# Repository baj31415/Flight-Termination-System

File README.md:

# FTS
Flight Termination System for SUAS 2018

This is the onboard flight termination system designed for the safety flight termination of an aircraft in the case of a telemetry or rc link loss. This system was used by my team SRMUAV's aircraft in the competition AUVSI SUAS 2018. Completely designed in Eagle CAD.

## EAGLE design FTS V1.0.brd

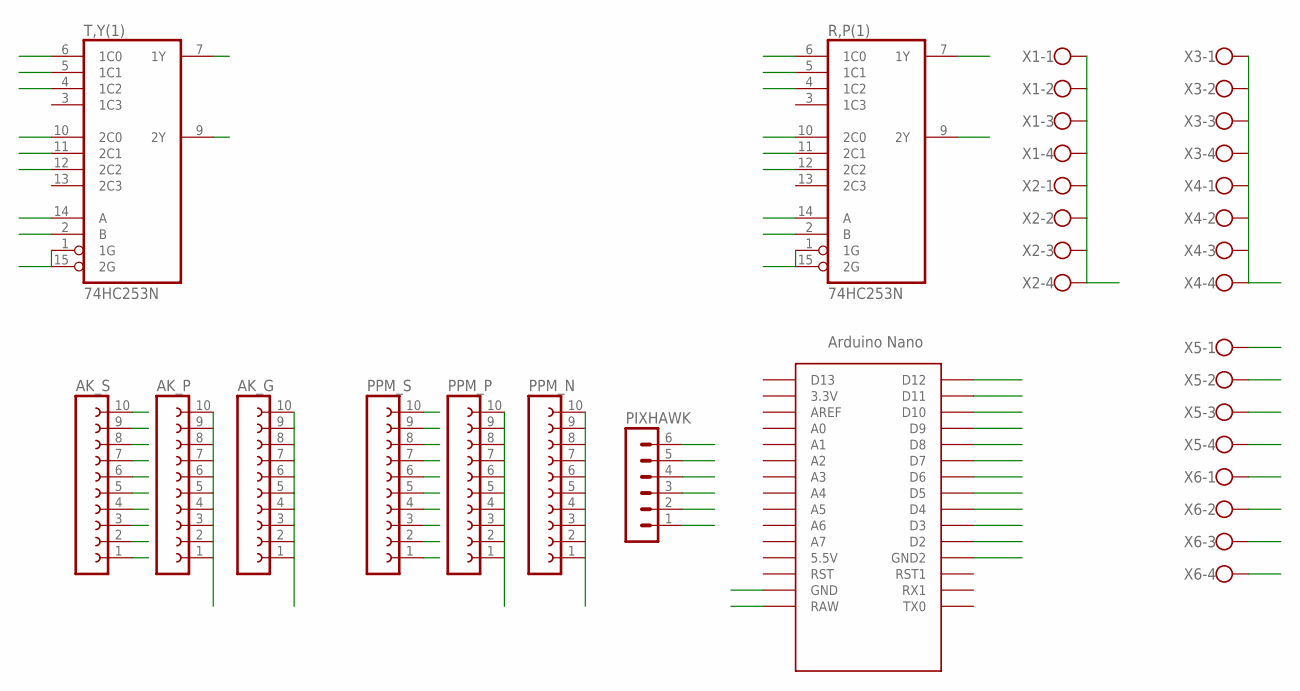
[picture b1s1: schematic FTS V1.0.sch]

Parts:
AK_G: FE10-1; FE10
AK_P: FE10-1; FE10
AK_S: FE10-1; FE10
PIXHAWK: MA06-1
PPM_N: FE10-1; FE10
PPM_P: FE10-1; FE10
PPM_S: FE10-1; FE10
R,P(1): 74HC253N; DIL16
T,Y(1): 74HC253N; DIL16
U$1: NANO
X1, X2, X3, X4, X5, X6: W237-4

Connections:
AUX2: AK_S.7, U$1.D4
DROP: AK_S.10, X6.4
FTS-P: R,P(1).12 (2C2), U$1.D10
FTS-R: R,P(1).4 (1C2), U$1.D9
FTS-T: T,Y(1).4 (1C2), U$1.D11
FTS-Y: T,Y(1).12 (2C2), U$1.D6
GBL-P: AK_S.9, X6.3
GBL-R: AK_S.8, X6.2
GEAR: AK_S.6, U$1.D5
GND: AK_G.1, AK_G.2, AK_G.3, AK_G.4, AK_G.5, AK_G.6, AK_G.7, AK_G.8, AK_G.9, AK_G.10, PIXHAWK.6, PPM_N.1, PPM_N.2, PPM_N.3, PPM_N.4, PPM_N.5, PPM_N.6, PPM_N.7, PPM_N.8, PPM_N.9, PPM_N.10, R,P(1).1 (1G), R,P(1).8 (GND), R,P(1).15 (2G), T,Y(1).1 (1G), T,Y(1).8 (GND), T,Y(1).15 (2G), U$1.GND, U$1.GND1 (GND2), X3.1, X3.2, X3.3, X3.4, X4.1, X4.2, X4.3, X4.4
PPM_FM: PPM_S.5, U$1.D8
PX-P: PIXHAWK.2, R,P(1).11 (2C1)
PX-R: PIXHAWK.1, R,P(1).5 (1C1)
PX-T: PIXHAWK.3, T,Y(1).5 (1C1)
PX-Y: PIXHAWK.4, T,Y(1).11 (2C1)
RX-FM: AK_S.5, U$1.D7
RX-P: AK_S.2, PPM_S.2, R,P(1).10 (2C0)
RX-R: AK_S.1, PPM_S.1, R,P(1).6 (1C0)
RX-T: AK_S.3, PPM_S.3, T,Y(1).6 (1C0), U$1.D12
RX-Y: AK_S.4, PPM_S.4, T,Y(1).10 (2C0)
S1: R,P(1).14 (A), T,Y(1).14 (A), U$1.D2
S2: R,P(1).2 (B), T,Y(1).2 (B), U$1.D3
S-P: R,P(1).9 (2Y), X5.2
S-R: R,P(1).7 (1Y), X5.1
S-T: T,Y(1).7 (1Y), X5.3
S-Y: T,Y(1).9 (2Y), X5.4, X6.1
VCC: AK_P.1, AK_P.2, AK_P.3, AK_P.4, AK_P.5, AK_P.6, AK_P.7, AK_P.8, AK_P.9, AK_P.10, PPM_P.1, PPM_P.2, PPM_P.3, PPM_P.4, PPM_P.5, PPM_P.6, PPM_P.7, PPM_P.8, PPM_P.9, PPM_P.10, R,P(1).16 (VCC), T,Y(1).16 (VCC), U$1.RAW, X1.1, X1.2, X1.3, X1.4, X2.1, X2.2, X2.3, X2.4

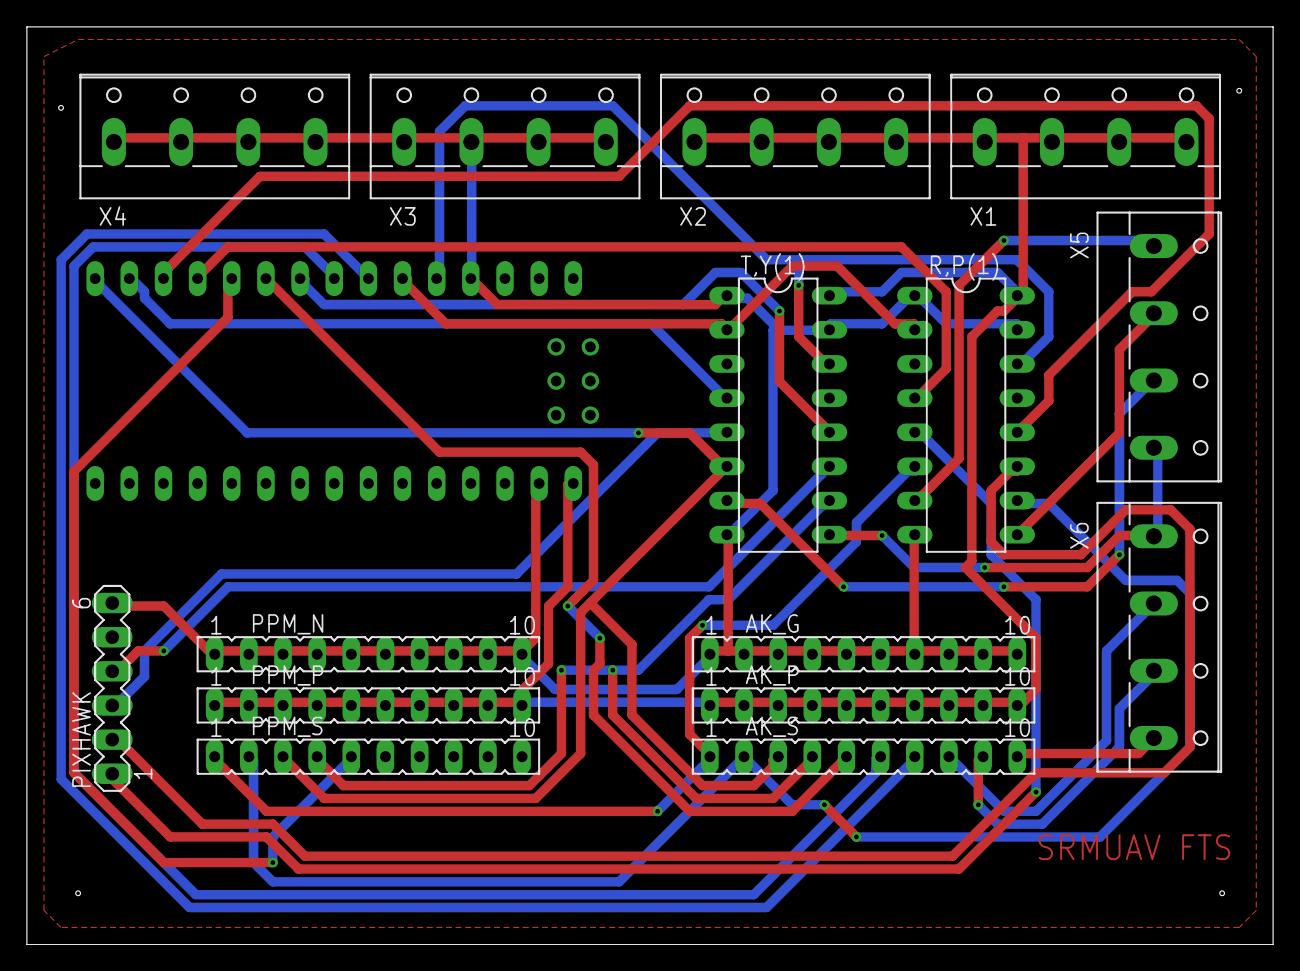
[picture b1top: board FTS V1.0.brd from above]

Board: 2 copper layers, 92.7 x 68.2 mm, 16 parts (0 on the bottom side), 27 nets.
